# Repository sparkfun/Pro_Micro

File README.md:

SparkFun Pro Micro and Qwiic Pro Micro USB-C
========================================

<table class="table table-hover table-striped table-bordered">
  <tr>
   <td><a href="https://www.sparkfun.com/products/12587"><div align="center"></div></a></td>
   <td><a href="https://www.sparkfun.com/products/12640"></div></a></center></td>
   <td><a href="https://www.sparkfun.com/products/15795"></div></a></center></td>
  </tr>
  <tr>
    <td><div align="center">Pro Micro - 3.3V/8MHz <br />[<a href="https://www.sparkfun.com/products/12587">DEV-12587</a>]</div></td>
    <td><div align="center">Pro Micro - 5V/16MHz <br />[<a href="https://www.sparkfun.com/products/12640">DEV-12640</a>]</div></td>
    <td><div align="center">Qwiic Pro Micro - USB-C (ATmega32U4) <br />[<a href="https://www.sparkfun.com/products/15795">DEV-15795</a>]</div></td>
  </tr>
</table>

The Pro Micro is a microcontroller with an ATMega32U4 IC on board. The USB transceiver is inside the 32U4, adding USB connectivity on-board without external USB interfaces. The Pro Micro comes in both a 3.3V and 5V version. For users using the Qwiic Pro Micro USB-C, the board includes a jumper to select either 5V or 3.3V, reset button, castellated pads, and Qwiic connector. The USB connector and voltage regulator are also different. 

Repository Contents
-------------------
* **/Documentation** - Data sheets (.pdf and .svg)
* **/Firmware** - Arduino example code used in the hookup guide
* **/Hardware** - All Eagle design files (.brd, .sch, .STL)
* **/Production** - Test bed files and production panel files

Documentation
--------------
* **Hookup Guide** 
  * **[Pro Micro & Fio V3](https://learn.sparkfun.com/tutorials/pro-micro--fio-v3-hookup-guide)** - Basic hookup guide for the Pro Micro (ATmega32U4) 3.3V and 5V versions as well as the Fio V3.
  * **[Qwiic Pro Micro USB-C](https://learn.sparkfun.com/tutorials/qwiic-pro-micro-usb-c-atmega32u4-hookup-guide)** - Basic hookup guide for the Qwiic Pro Micro.
* **[SparkFun Arduino Board Addon](https://github.com/sparkfun/Arduino_Boards/)** - Arduino board addon for Qwiic Pro Micro.
* **[SparkFun Graphical Datasheets](https://github.com/sparkfun/Graphical_Datasheets)** - Graphical datasheets for various SparkFun products.
* **[SparkFun Fritzing repo](https://github.com/sparkfun/Fritzing_Parts)** - Fritzing diagrams for SparkFun products.

Product Versions
----------------
* [DEV-15795](https://www.sparkfun.com/products/15795)- 5V/16MHz version with Qwiic connector and USB C
* [DEV-12640](https://www.sparkfun.com/products/12640)- 5V/16MHz version
* [DEV-12587](https://www.sparkfun.com/products/12587)- 3.3V/8MHz version

License Information
-------------------
This product is _**open source**_! 

Please review the LICENSE.md file for license information. 

If you have any questions or concerns on licensing, please contact technical support on our [SparkFun forums](https://forum.sparkfun.com/viewforum.php?f=152).

Distributed as-is; no warranty is given.

- Your friends at SparkFun.

_<COLLABORATION CREDIT>_

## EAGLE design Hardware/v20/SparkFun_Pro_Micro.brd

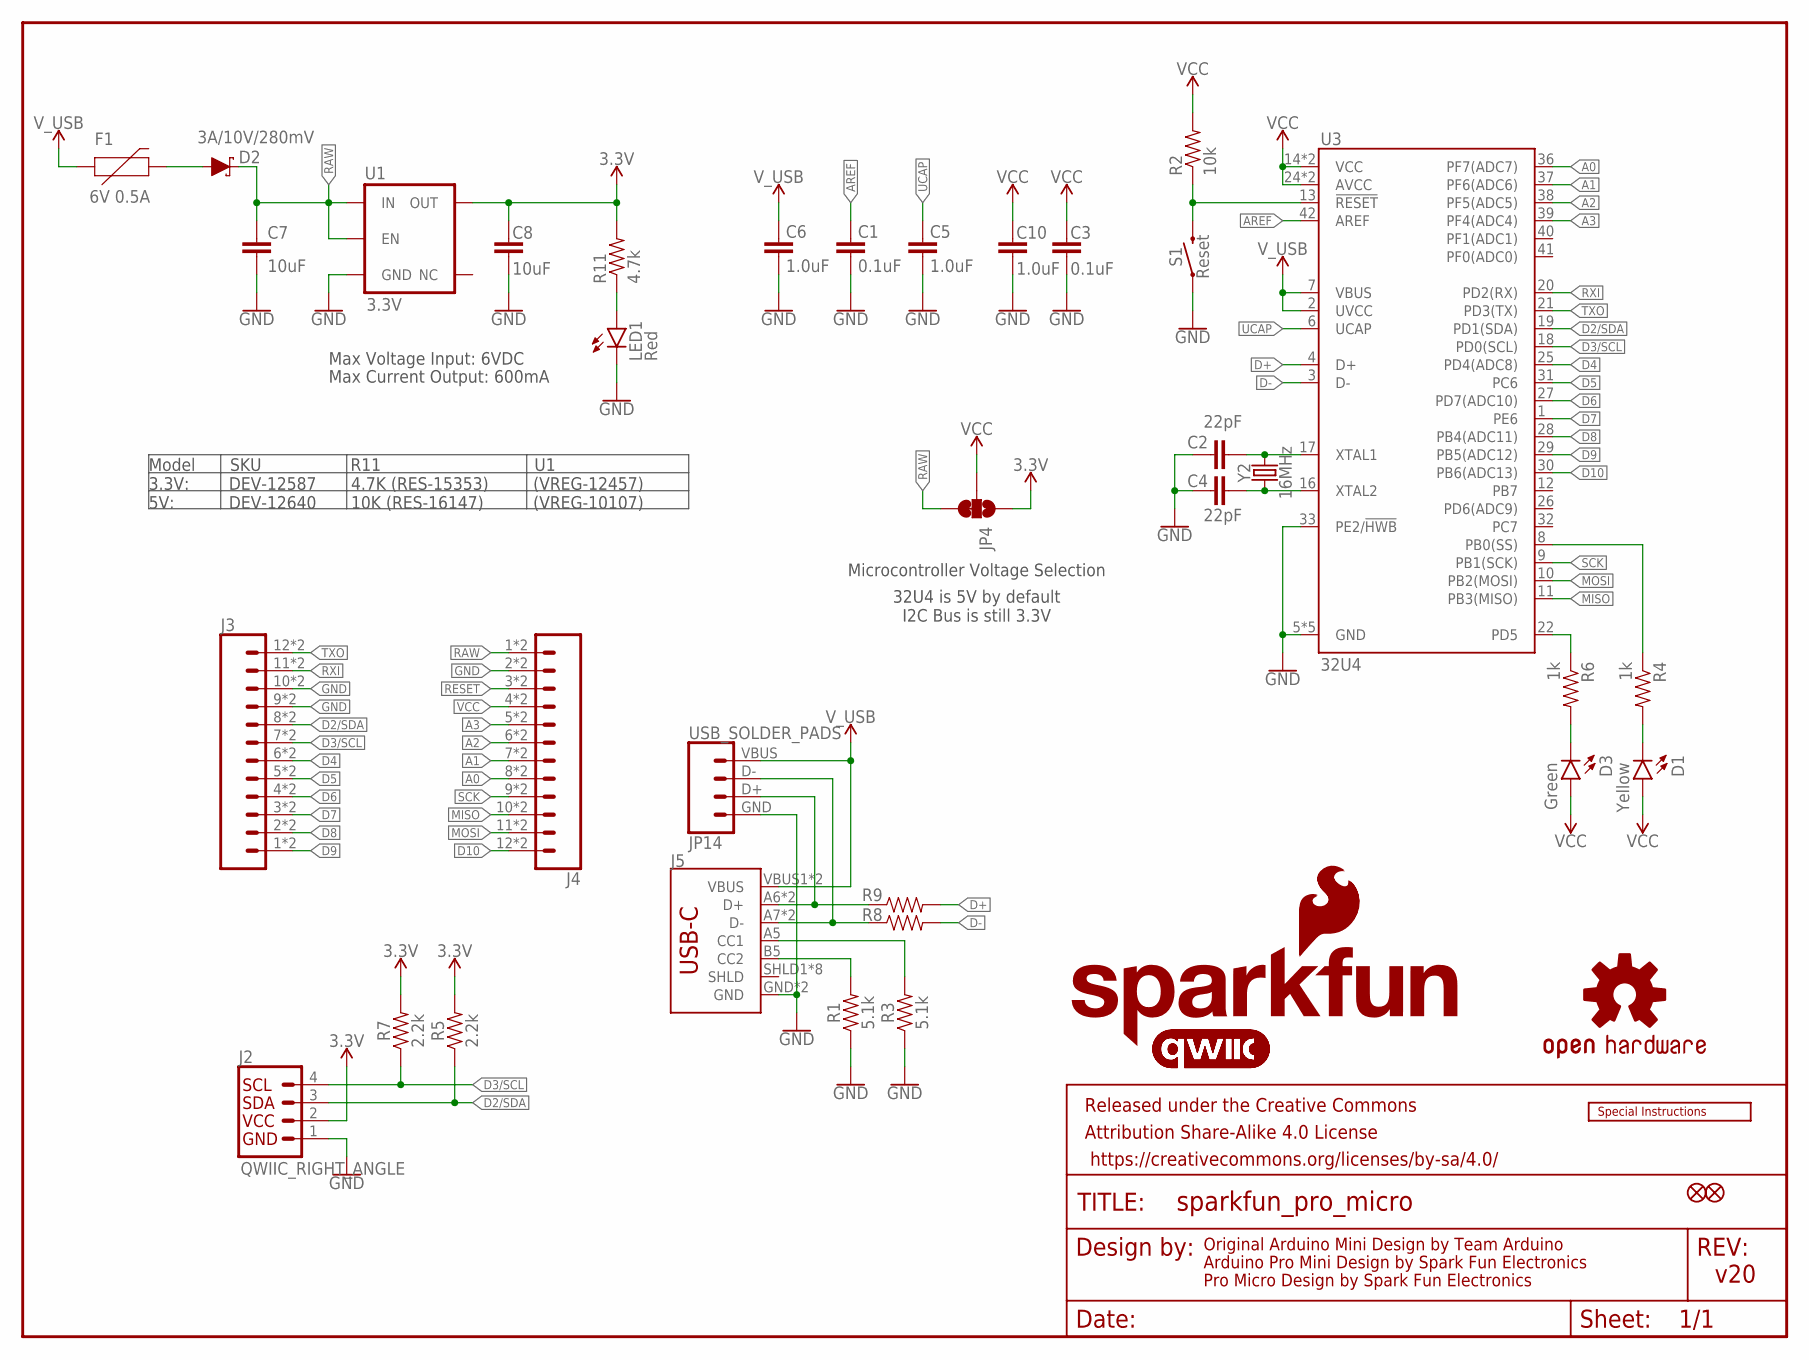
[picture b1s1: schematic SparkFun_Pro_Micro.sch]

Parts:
C1, C3: 0.1uF; 0402-TIGHT
C2, C4: 22pF; 0402-TIGHT
C5, C6, C10: 1.0uF; 0402-TIGHT
C7, C8: 10uF; 0603
D1: Yellow; LED-0603
D2: 3A/10V/280mV; SOD-323
D3: Green; LED-0603
F1: 6V 0.5A; 0805
FRAME1: FRAME-LETTER; CREATIVE_COMMONS
J2: QWIIC_RIGHT_ANGLE; JST04_1MM_RA
J3, J4: CONN_12CASTLE; 1X12_CASTELLATED
J5: USB_C5; USB-C-16P-5
JP1, JP2: FIDUCIAL1X2; FIDUCIAL-1X2
JP4: JUMPER-SMT_3_1-NC_TRACE_SILK; SMT-JUMPER_3_1-NC_TRACE_SILK
JP14: USB_SOLDER_PADS; USB-SOLDER-PADS
LED1: Red; LED-0603
LOGO1: SFE_LOGO_NAME_FLAME.1_INCH; SFE_LOGO_NAME_FLAME_.1
LOGO2: QWIIC_LOGO_4MM; QWIIC_4MM
LOGO3: QWIIC_LOGO_6MM; QWIIC_6MM
LOGO4: SFE_LOGO_FLAME.1_INCH; SFE_LOGO_FLAME_.1
LOGO5: SPECIAL_INSTRUCTIONS-ORDERING; ORDERING_INSTRUCTIONS
R1, R3: 5.1k; 0402-TIGHT
R2: 10k; 0402-TIGHT
R4, R6: 1k; 0402-TIGHT
R5, R7: 2.2k; 0402-TIGHT
R8, R9: 22Ω; 0402-TIGHT
R11: 4.7k; 0402-TIGHT
S1: Reset; TACTILE_SWITCH_SMD_4.6X2.8MM
U1: 3.3V; SOT23-5
U3: 32U4; QFN-44-NOPAD_1:1-LESS_PASTE
U$3: OSHW-LOGOMINI; OSHW-LOGO-MINI
Y2: 16MHz; CRYSTAL-SMD-2.0X1.6MM

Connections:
3.3V: C8.2, J2.2, JP4.1, R5.2, R7.2, R11.2, U1.5 (OUT)
A0: J4.8, J4.8B (8), U3.36 (PF7(ADC7))
A1: J4.7, J4.7B (7), U3.37 (PF6(ADC6))
A2: J4.6, J4.6B (6), U3.38 (PF5(ADC5))
A3: J4.5, J4.5B (5), U3.39 (PF4(ADC4))
AREF: C1.2, U3.42 (AREF)
D2/SDA: J2.3, J3.8, J3.8B (8), R5.1, U3.19 (PD1(SDA))
D3/SCL: J2.4, J3.7, J3.7B (7), R7.1, U3.18 (PD0(SCL))
D4: J3.6, J3.6B (6), U3.25 (PD4(ADC8))
D5: J3.5, J3.5B (5), U3.31 (PC6)
D6: J3.4, J3.4B (4), U3.27 (PD7(ADC10))
D7: J3.3, J3.3B (3), U3.1 (PE6)
D8: J3.2, J3.2B (2), U3.28 (PB4(ADC11))
D9: J3.1, J3.1B (1), U3.29 (PB5(ADC12))
D10: J4.12, J4.12B (12), U3.30 (PB6(ADC13))
D+: R9.2, U3.4 (D+)
D-: R8.2, U3.3 (D-)
D-_HV: J5.A7 (D-), J5.B7 (D-), JP14.D- (2), R8.1
DP_HV: J5.A6 (D+), J5.B6 (D+), JP14.D+ (3), R9.1
GND: C1.1, C2.2, C3.1, C4.2, C5.1, C6.1, C7.1, C8.1, C10.1, J2.1, J3.9, J3.9B (9), J3.10, J3.10B (10), J4.2, J4.2B (2), J5.GND, J5.GND2 (GND), JP14.GND (4), LED1.C, R1.1, R3.1, S1.1, S1.2 (1), U1.2 (GND), U3.5 (GND), U3.15 (GND), U3.23 (GND), U3.33 (PE2/!HWB), U3.35 (GND), U3.43 (GND)
MISO: J4.10, J4.10B (10), U3.11 (PB3(MISO))
MOSI: J4.11, J4.11B (11), U3.10 (PB2(MOSI))
unnamed: C4.1, U3.16 (XTAL2), Y2.1
unnamed: C2.1, U3.17 (XTAL1), Y2.3 (2)
unnamed: D1.C, R4.2
unnamed: D3.C, R6.2
unnamed: J5.A5 (CC1), R3.2
unnamed: J5.B5 (CC2), R1.2
unnamed: LED1.A, R11.1
RAW: C7.2, D2.C, J4.1, J4.1B (1), JP4.3, U1.1 (IN), U1.3 (EN)
RESET: J4.3, J4.3B (3), R2.1, S1.3 (2), S1.4 (2), U3.13 (!RESET)
RXI: J3.11, J3.11B (11), U3.20 (PD2(RX))
RXLED: R4.1, U3.8 (PB0(SS))
SCK: J4.9, J4.9B (9), U3.9 (PB1(SCK))
TXLED: R6.1, U3.22 (PD5)
TXO: J3.12, J3.12B (12), U3.21 (PD3(TX))
UCAP: C5.2, U3.6 (UCAP)
USB_RAW: D2.A, F1.2
VCC: C3.2, C10.2, D1.A, D3.A, J4.4, J4.4B (4), JP4.2, R2.2, U3.14 (VCC), U3.24 (AVCC), U3.34 (VCC), U3.44 (AVCC)
V_USB: C6.2, F1.1, J5.VBUS1 (VBUS), J5.VBUS2 (VBUS), JP14.VBUS (1), U3.2 (UVCC), U3.7 (VBUS)

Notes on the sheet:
Original Arduino Mini Design by Team Arduino
Arduino Pro Mini Design by Spark Fun Electronics
Max Voltage Input: 6VDC
Max Current Output: 600mA
Pro Micro Design by Spark Fun Electronics
Microcontroller Voltage Selection
v20
32U4 is 5V by default I2C Bus is still 3.3V
Model SKU R11 U1 3.3V: DEV-12587 4.7K (RES-15353) (VREG-12457) 5V: DEV-12640 10K (RES-16147) (VREG-10107)

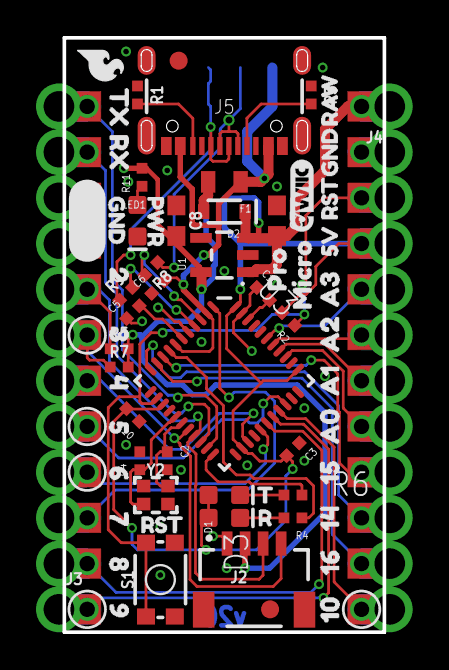
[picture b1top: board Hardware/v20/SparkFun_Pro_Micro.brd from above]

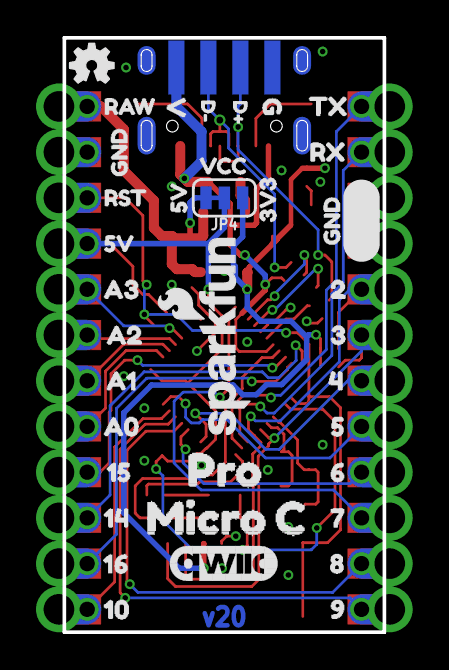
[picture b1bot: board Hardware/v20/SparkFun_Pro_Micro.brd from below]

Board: 2 copper layers, 17.8 x 33.0 mm, 105 parts (38 on the bottom side), 40 nets.

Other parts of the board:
U$1: VCC1
U$2, U$38: 156
U$4, U$48: 164
U$5, U$57: 218
U$6, U$56: 317
U$7, U$54: 515
U$8, U$53: 614
U$9, U$52: 713
U$10, U$51: 812
U$11, U$22, U$32, U$58: GND4
U$12, U$46: RAW5
U$13, U$55: 45
U$14: T8
U$15, U$64, U$65: 5V1
U$16, U$50: 911
U$17, U$37: A07
U$18, U$60: TX2
U$19, U$36: A18
U$21, U$49: 104
U$23: MICRO1
U$24: PRO0
U$25, U$31, U$41: RST3
U$26, U$35: A29
U$27, U$34: A310
U$28, U$59: RX20
U$29, U$47: 145
U$30: R9
U$39: 3V39
U$40: C5
U$42: G1
U$43: MICRO4
U$44: V0
U$45: PRO3
U$61: D#3
U$62: D#4
U$63: PWR0

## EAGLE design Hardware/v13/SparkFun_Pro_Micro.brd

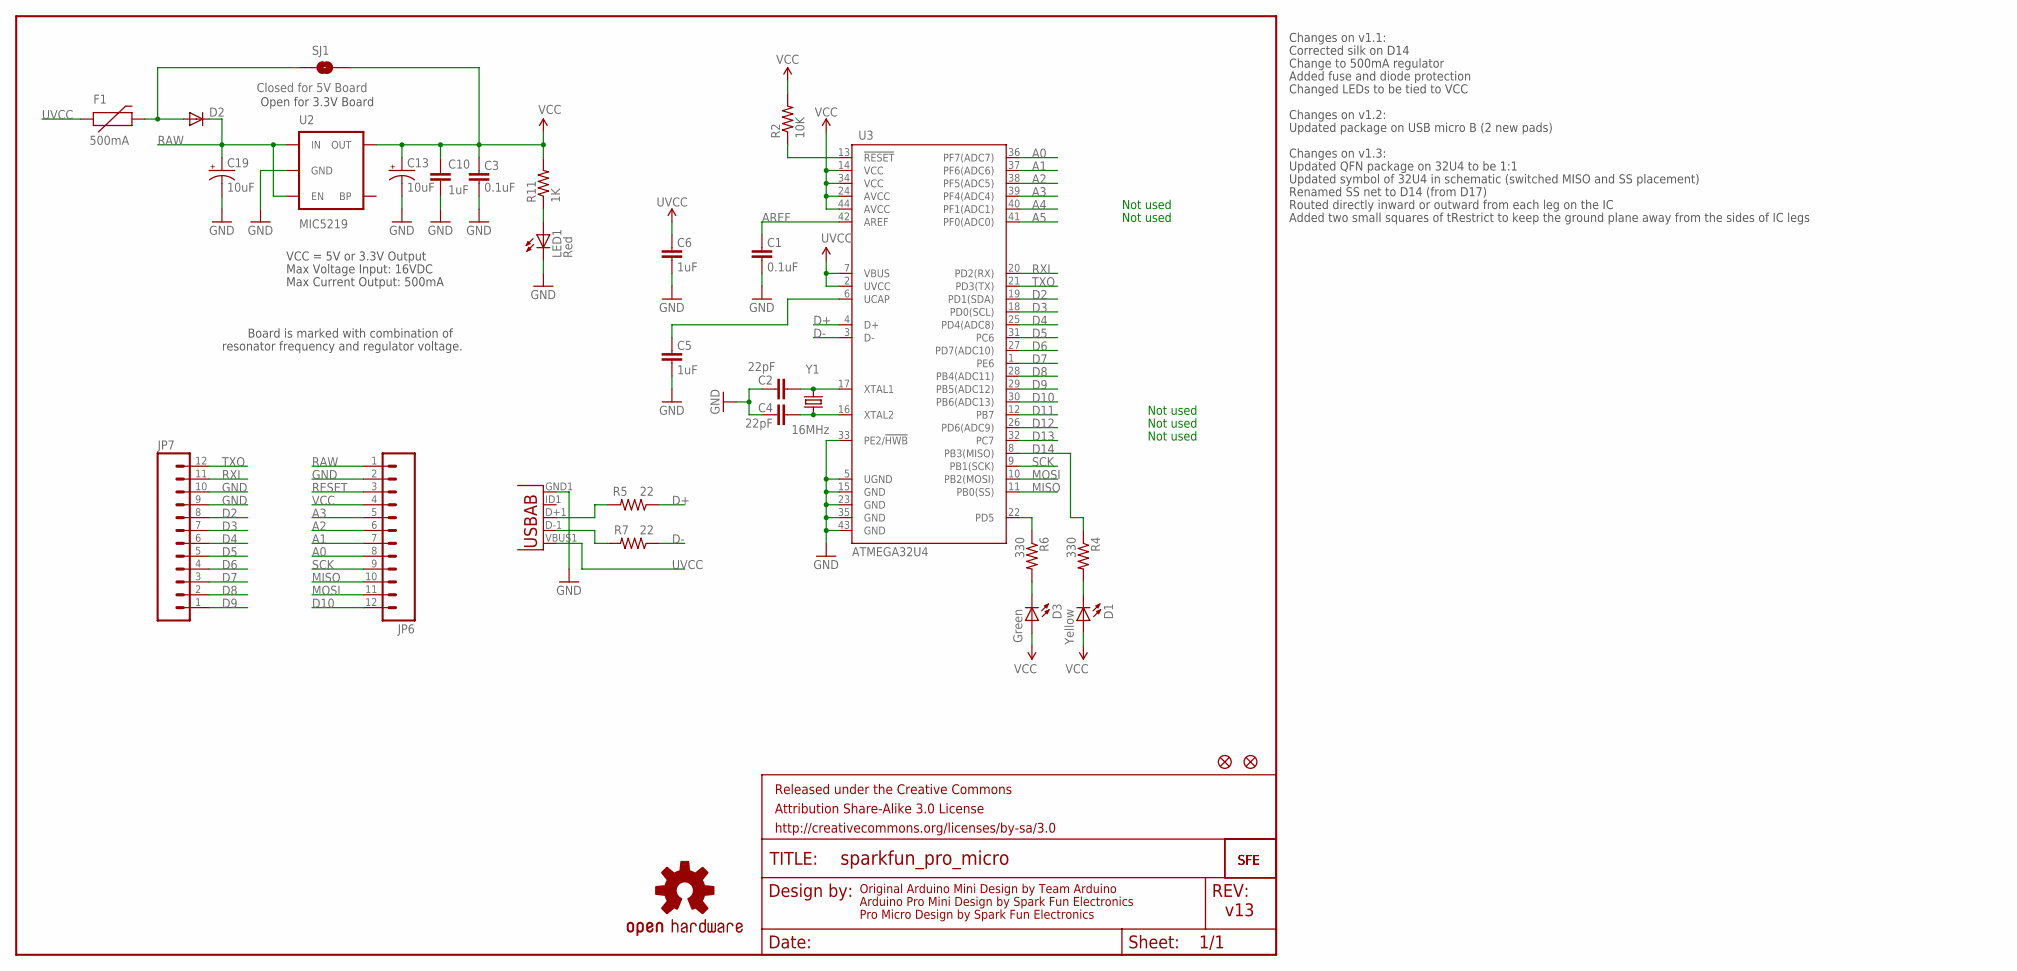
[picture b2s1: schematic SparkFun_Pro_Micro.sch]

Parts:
C1, C3: 0.1uF; 0603-CAP
C2, C4: 22pF; 0603-CAP
C5, C6, C10: 1uF; 0603-CAP
C13, C19: 10uF; EIA3216
D1: Yellow; LED-0603
D2: DIODESOD; SOD-323
D3: Green; LED-0603
F1: 500mA; PTC-1206
FRAME1: FRAME-LETTER; CREATIVE_COMMONS
JP1, JP2: FIDUCIALUFIDUCIAL; MICRO-FIDUCIAL
JP6, JP7: M12PTH; 1X12
LED1: Red; LED-0603
R2: 10K; 0603-RES
R4, R6: 330; 0603-RES
R5, R7: 22; 0603-RES
R11: 1K; 0603-RES
SJ1: Closed for 5V Board; SJ_2S
U2: MIC5219; SOT23-5
U3: ATMEGA32U4; QFN-44-NOPAD_1:1-OUTFAKES
U$1: LOGO-SFESK; SFE-LOGO-FLAME
U$3: OSHW-LOGOS; OSHW-LOGO-S
U$11: LOGO-SFENEW; SFE-NEW-WEBLOGO
X1: USB-ABIN&OUT; USB-AB-MICRO-SMD-V03-IN&OUT
Y1: 16MHz; CRYSTAL-SMD-5X3

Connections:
A0: JP6.8, U3.36 (PF7(ADC7))
A1: JP6.7, U3.37 (PF6(ADC6))
A2: JP6.6, U3.38 (PF5(ADC5))
A3: JP6.5, U3.39 (PF4(ADC4))
A4: U3.40 (PF1(ADC1))
A5: U3.41 (PF0(ADC0))
AREF: C1.2, U3.42 (AREF)
D2: JP7.8, U3.19 (PD1(SDA))
D3: JP7.7, U3.18 (PD0(SCL))
D4: JP7.6, U3.25 (PD4(ADC8))
D5: JP7.5, U3.31 (PC6)
D6: JP7.4, U3.27 (PD7(ADC10))
D7: JP7.3, U3.1 (PE6)
D8: JP7.2, U3.28 (PB4(ADC11))
D9: JP7.1, U3.29 (PB5(ADC12))
D10: JP6.12, U3.30 (PB6(ADC13))
D11: U3.12 (PB7)
D12: U3.26 (PD6(ADC9))
D13: U3.32 (PC7)
D14: R4.1, U3.8 (PB3(MISO))
D+: R5.1, U3.4 (D+)
D-: R7.1, U3.3 (D-)
GND: C1.1, C2.2, C3.1, C4.2, C5.1, C6.1, C10.2, C13.C (-), C19.C (-), JP6.2, JP7.9, JP7.10, LED1.C, U2.2 (GND), U3.5 (UGND), U3.15 (GND), U3.23 (GND), U3.33 (PE2/!HWB), U3.35 (GND), U3.43 (GND), X1.GND1 (GND)
MISO: JP6.10, U3.11 (PB0(SS))
MOSI: JP6.11, U3.10 (PB2(MOSI))
unnamed: C4.1, U3.16 (XTAL2), Y1.1
unnamed: C2.1, U3.17 (XTAL1), Y1.3 (2)
unnamed: D2.2 (A), F1.2, SJ1.1
unnamed: C5.2, U3.6 (UCAP)
unnamed: D1.C, R4.2
unnamed: R7.2, X1.D-1 (D-)
unnamed: D3.C, R6.2
unnamed: R5.2, X1.D+1 (D+)
unnamed: LED1.A, R11.1
RAW: C19.A (+), D2.1 (C), JP6.1, U2.1 (IN), U2.3 (EN)
RESET: JP6.3, R2.1, U3.13 (!RESET)
RXI: JP7.11, U3.20 (PD2(RX))
SCK: JP6.9, U3.9 (PB1(SCK))
TXLED: R6.1, U3.22 (PD5)
TXO: JP7.12, U3.21 (PD3(TX))
UVCC: C6.2, F1.1, U3.2 (UVCC), U3.7 (VBUS), X1.VBUS1 (VBUS)
VCC: C3.2, C10.1, C13.A (+), D1.A, D3.A, JP6.4, R2.2, R11.2, SJ1.2, U2.5 (OUT), U3.14 (VCC), U3.24 (AVCC), U3.34 (VCC), U3.44 (AVCC)

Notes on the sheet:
Original Arduino Mini Design by Team Arduino
Arduino Pro Mini Design by Spark Fun Electronics
Max Voltage Input: 16VDC
Max Current Output: 500mA
Board is marked with combination of
resonator frequency and regulator voltage.
VCC = 5V or 3.3V Output
Not used
Pro Micro Design by Spark Fun Electronics
Changes on v1.1:
Corrected silk on D14
Change to 500mA regulator
Open for 3.3V Board
Added fuse and diode protection
Changed LEDs to be tied to VCC
Changes on v1.2:
Updated package on USB micro B (2 new pads)
Changes on v1.3:
Updated QFN package on 32U4 to be 1:1
Updated symbol of 32U4 in schematic (switched MISO and SS placement)
Renamed SS net to D14 (from D17)
Routed directly inward or outward from each leg on the IC
Added two small squares of tRestrict to keep the ground plane away from the sides of IC legs
v13

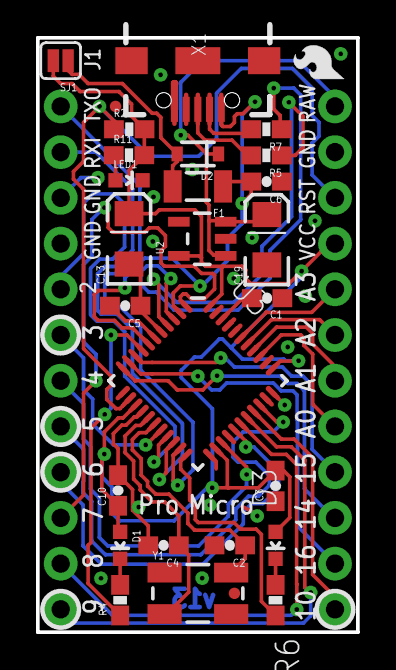
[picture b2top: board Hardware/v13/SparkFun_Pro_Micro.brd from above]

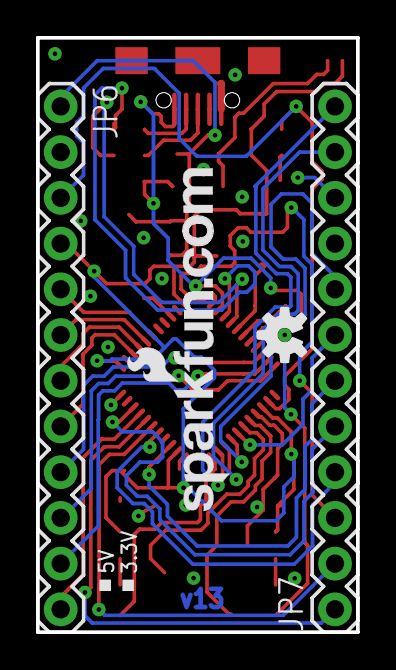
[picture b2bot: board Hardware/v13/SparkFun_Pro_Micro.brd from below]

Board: 2 copper layers, 17.8 x 33.0 mm, 33 parts (4 on the bottom side), 37 nets.

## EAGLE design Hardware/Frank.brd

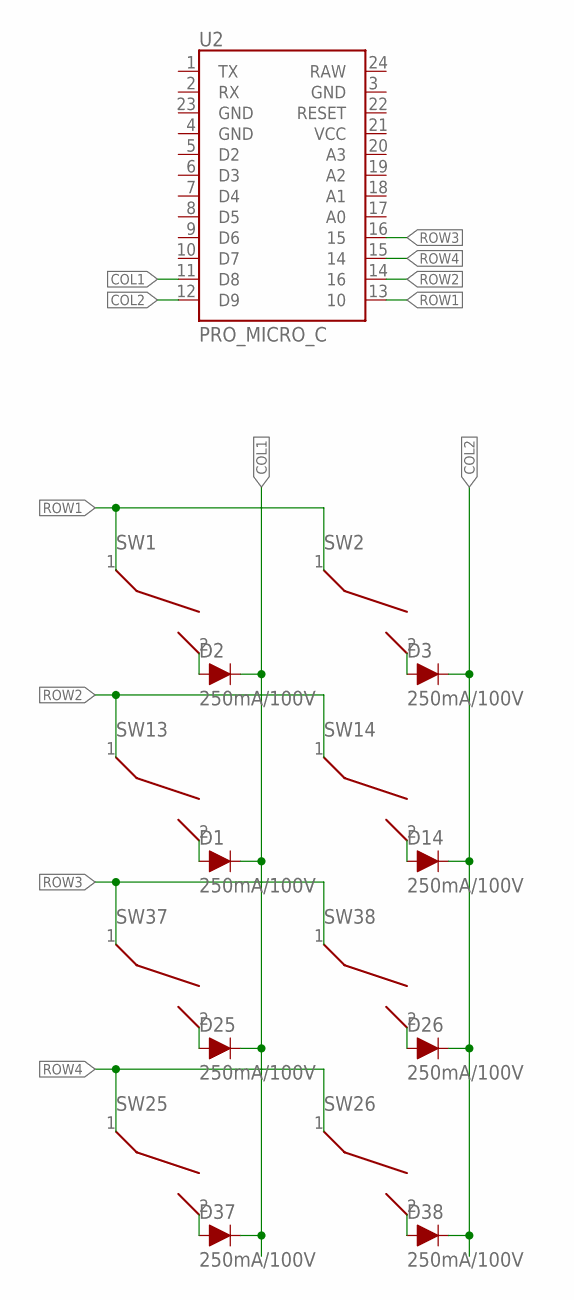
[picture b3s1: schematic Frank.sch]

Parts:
D1, D2, D3, D14, D25, D26, D37, D38: 250mA/100V; SOD-323
SW1, SW2, SW13, SW14, SW25, SW26, SW37, SW38: CHERRY_MX_WITH_FIXING_PINS; MX1A-XXNW
U2: PRO_MICRO_C

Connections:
COL1: D1.C, D2.C, D25.C, D37.C, U2.11 (D8)
COL2: D3.C, D14.C, D26.C, D38.C, U2.12 (D9)
unnamed: D2.A, SW1.2
unnamed: D3.A, SW2.2
unnamed: D1.A, SW13.2
unnamed: D25.A, SW37.2
unnamed: D37.A, SW25.2
unnamed: D38.A, SW26.2
unnamed: D26.A, SW38.2
unnamed: D14.A, SW14.2
ROW1: SW1.1, SW2.1, U2.13 (10)
ROW2: SW13.1, SW14.1, U2.14 (16)
ROW3: SW37.1, SW38.1, U2.16 (15)
ROW4: SW25.1, SW26.1, U2.15 (14)

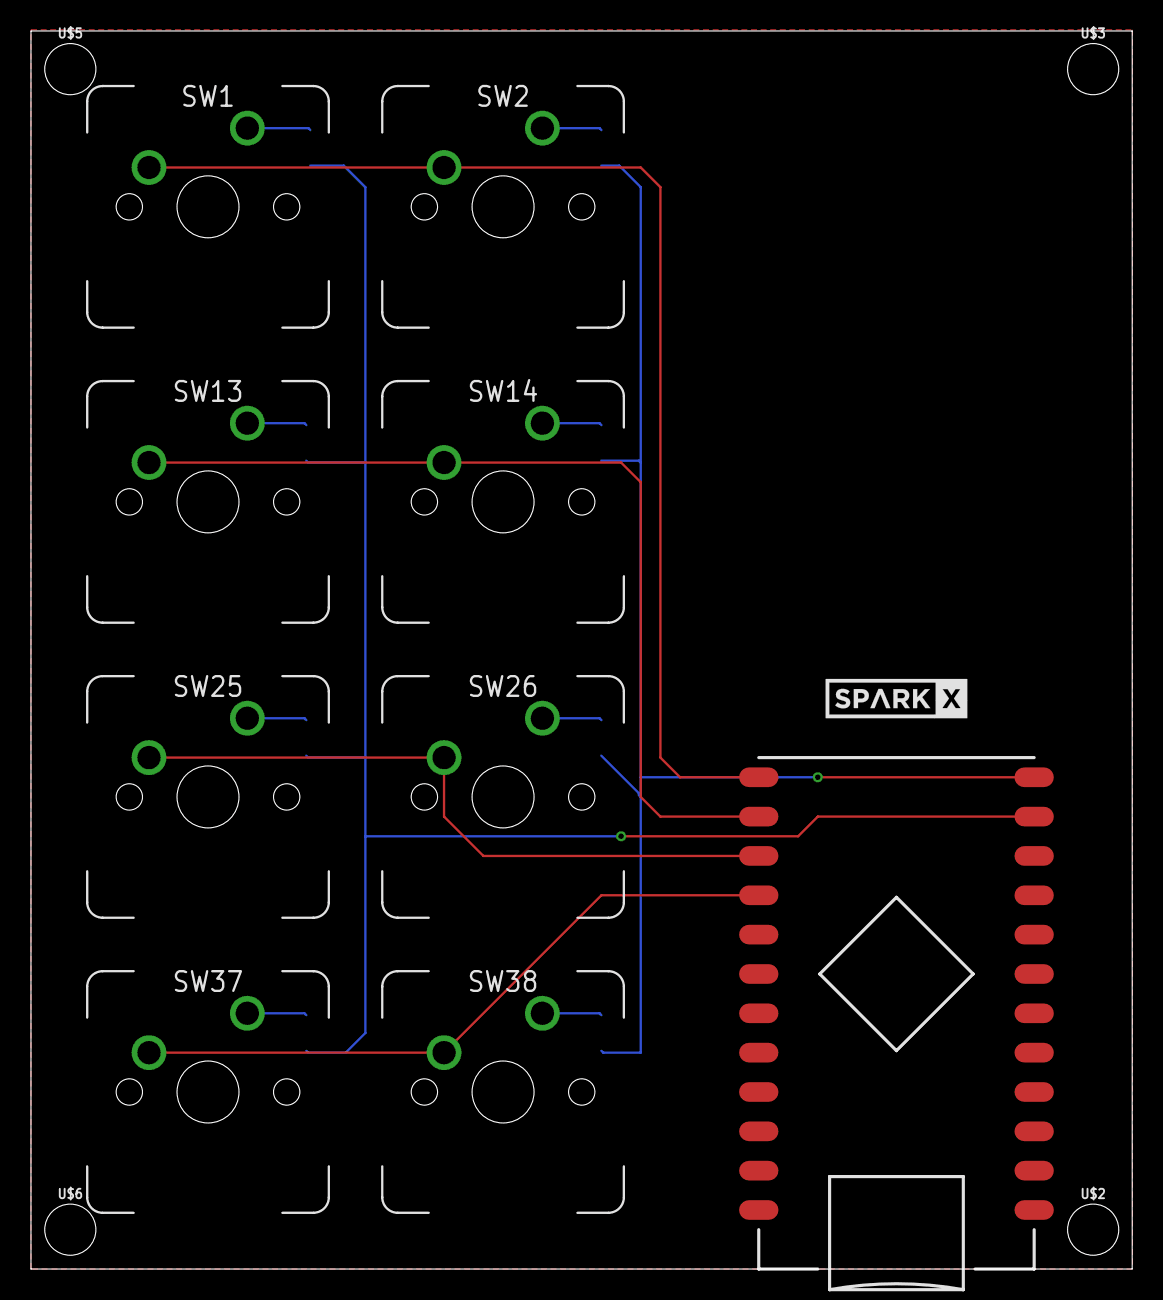
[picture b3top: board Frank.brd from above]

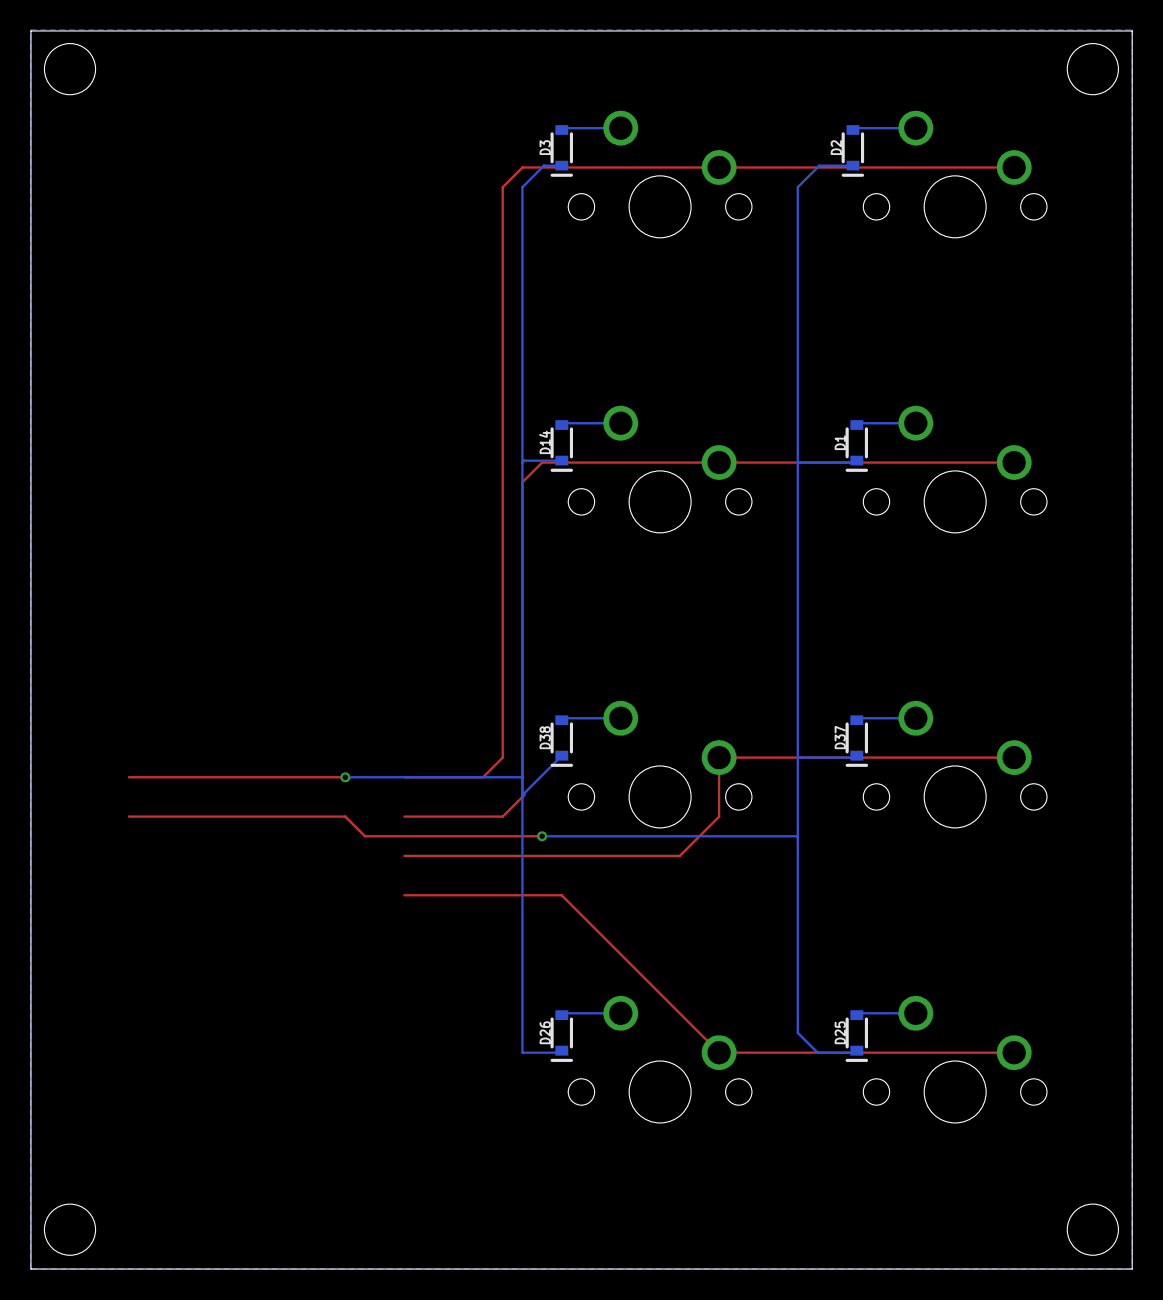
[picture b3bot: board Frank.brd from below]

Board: 2 copper layers, 71.1 x 79.9 mm, 22 parts (8 on the bottom side), 14 nets.

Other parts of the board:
U$2, U$3, U$5, U$6: STAND-OFF
U$7: SPARKX-MEDIUM

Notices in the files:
parts and their libraries:
SparkFun-DiscreteSemi: Licensing: Creative Commons ShareAlike 4.0 International - https://creativecommons.org/licenses/by-sa/4.0
SparkFun-Aesthetics: Licensing: CC v3.0 Share-Alike You are welcome to use this library for commercial purposes.
SparkFun-Aesthetics: Released under the Creative Commons
